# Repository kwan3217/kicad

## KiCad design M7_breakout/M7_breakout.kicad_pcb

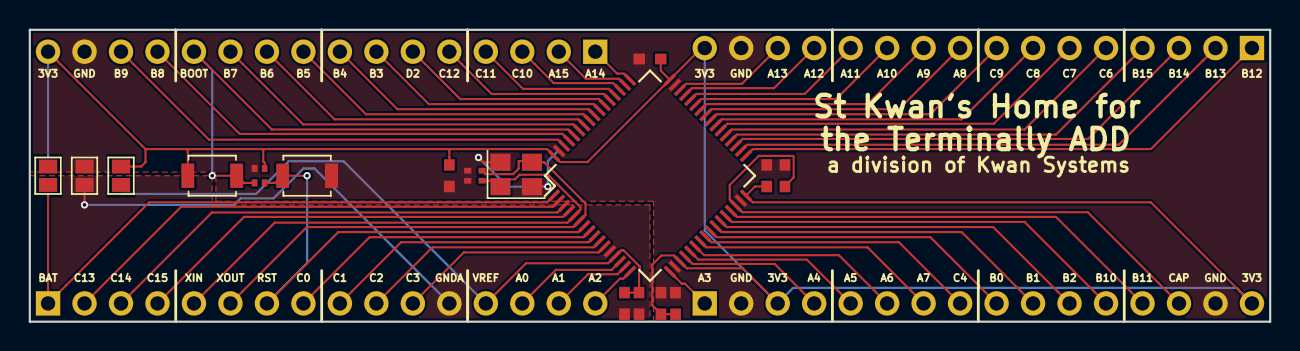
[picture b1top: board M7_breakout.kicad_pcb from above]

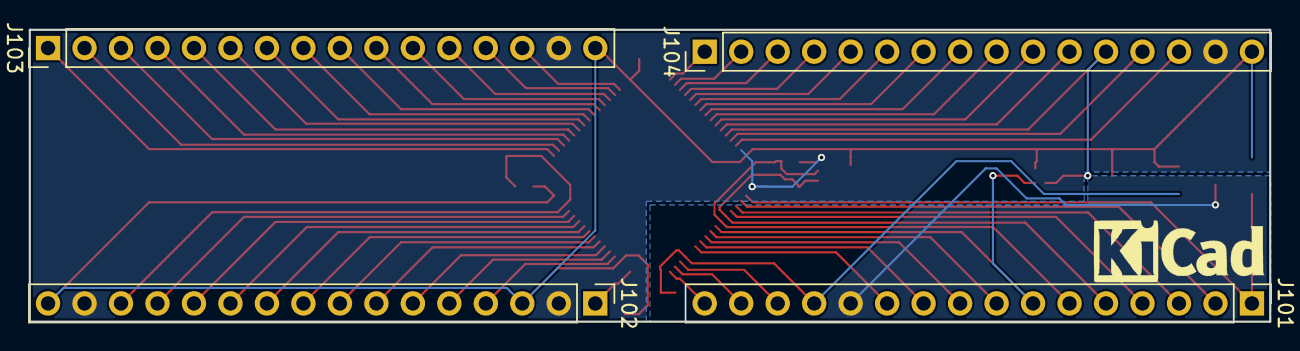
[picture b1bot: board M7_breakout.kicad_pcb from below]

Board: 2 copper layers, 86.4 x 20.3 mm, 21 parts (4 on the bottom side), 58 nets.

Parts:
C105: 22pF; R_Array_Convex_2x0402
C112: 1uF; SMD_0603
C113: 10nF; SMD_0603
C118, C130: 4.7uF; SMD_0603
C119, C132, C148, C164: 100nF; SMD_0603
J101, J102, J103, J104: Conn_01x16; Pin_Header_Straight_1x16_Pitch2.54mm
R107: 10k; R_Array_Convex_2x0402
S101, S112, S113: GS2
S107, S160: SW_SPST; SW_SPST_B3U-1000P
U101: STM32F722; LQFP-64_10x10mm_Pitch0.5mm
Y101: 12MHz; Crystal_SMD_3225-4pin_3.2x2.5mm

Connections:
+3V3: C118.2, C119.2, C132.2, C148.2, C164.2, J102.3, J102.16, J103.16, J104.16, R107.1, S101.2, S113.2, S160.1, U101.19, U101.32, U101.48, U101.64
/BOOT: J104.12, R107.3, S160.2, U101.60
/P2: J101.2, U101.2
/P3: J101.3, U101.3
/P4: J101.4, U101.4
/P8: J101.8, U101.8
/P9: J101.9, U101.9
/P10: J101.10, U101.10
/P11: J101.11, U101.11
/P14: J101.14, U101.14
/P15: J101.15, U101.15
/P16: J101.16, U101.16
/P17: J102.1, U101.17
/P20: J102.4, U101.20
/P21: J102.5, U101.21
/P22: J102.6, U101.22
/P23: J102.7, U101.23
/P24: J102.8, U101.24
/P25: J102.9, U101.25
/P26: J102.10, U101.26
/P27: J102.11, U101.27
/P28: J102.12, U101.28
/P29: J102.13, U101.29
/P33: J103.1, U101.33
/P34: J103.2, U101.34
/P35: J103.3, U101.35
/P36: J103.4, U101.36
/P37: J103.5, U101.37
/P38: J103.6, U101.38
/P39: J103.7, U101.39
/P40: J103.8, U101.40
/P41: J103.9, U101.41
/P42: J103.10, U101.42
/P43: J103.11, U101.43
/P44: J103.12, U101.44
/P45: J103.13, U101.45
/P46: J103.14, U101.46
/P49: J104.1, U101.49
/P50: J104.2, U101.50
/P51: J104.3, U101.51
/P52: J104.4, U101.52
/P53: J104.5, U101.53
/P54: J104.6, U101.54
/P55: J104.7, U101.55
/P56: J104.8, U101.56
/P57: J104.9, U101.57
/P58: J104.10, U101.58
/P59: J104.11, U101.59
/P61: J104.13, U101.61
/P62: J104.14, U101.62
/RESET: J101.7, R107.4, S107.1, U101.7
/VBAT: J101.1, S101.1, U101.1
/VCAP: C130.2, J102.14, U101.30
/VREF+: C112.2, C113.2, J101.13, S113.1, U101.13
/VSSA: C112.1, C113.1, J101.12, S112.1, U101.12
/XIN: C105.3, J101.5, U101.5, Y101.1
/XOUT: C105.4, J101.6, U101.6, Y101.3
GND: C105.1, C105.2, C118.1, C119.1, C130.1, C132.1, C148.1, C164.1, J102.2, J102.15, J103.15, J104.15, R107.2, S107.2, S112.2, U101.18, U101.31, U101.47, U101.63, Y101.2, Y101.4

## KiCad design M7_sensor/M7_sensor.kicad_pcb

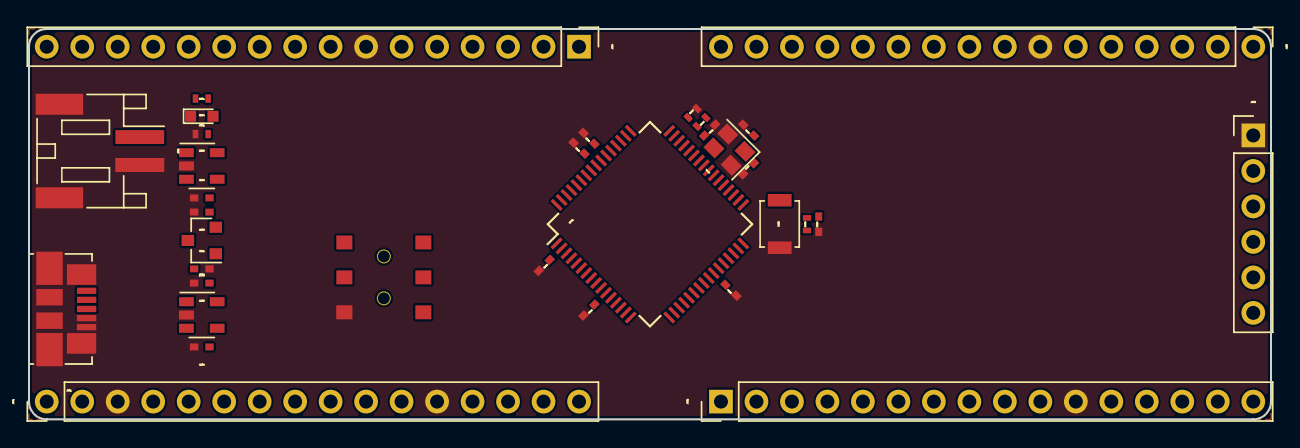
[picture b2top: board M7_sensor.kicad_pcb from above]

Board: 2 copper layers, 88.9 x 27.9 mm, 35 parts (1 on the bottom side), 23 nets, no tracks yet.

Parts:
C201, C205, C303, C304: 4.7uF; C_0402_NoSilk
C204, C402, C411, C426, C438, C442, C454: 100nF; C_0402_NoSilk
C440, C441: 22pF; C_0402_NoSilk
C456: 3.3uF; C_0402_NoSilk
D301: Yellow; LED_0603
D302: PMEG2005CT; SOT-23
J001: USB_OTG; USB_Micro-B_Molex_47346-0001
J301: Battery_Cell; JST_PH_S2B-PH-SM4-TB_02x2.00mm_Angled
J401, J402, J403, J404: CONN_01X16; Pin_Header_Straight_1x16_Pitch2.54mm
J405: CONN_01X06; Pin_Header_Straight_1x06_Pitch2.54mm
J701: Micro_SD_Card_SPI; MICROSD-SOCKET-PP
R304, R305, R438, R446: 10k; R_0402_NoSilk
R447: 22k; R_0402_NoSilk
S203: SW_DPDT_x2; SWITCH_DPDT_AZY0202
S438: SW_Push; SW_SPST_B3U-1000P
U201: MIC5319-3.3; SOT-23-5
U301: MCP73831; SOT-23-5
U401: ATSAMS70J; LQFP-64_10x10mm_Pitch0.5mm
Y440: 25MHz; Crystal_SMD_2520-4pin_2.5x2.0mm

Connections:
+3V3: C205.1, C402.1, C411.1, C426.1, C442.1, C454.1, J401.2, J401.11, J402.10, J403.10, J404.6, J405.3, J701.4, R438.1, U201.5
/BYPASS: C204.1, U201.4
/CS_SD: J402.4, J701.2
/D+: J001.3, J403.12
/D-: J001.2, J403.11
/ENABLE: S203.2, U201.3
/MISO0: J402.5, J701.7
/MOSI0: J402.6, J701.3
/OSC0: C440.2, J403.8, Y440.1
/OSC1: C441.2, J403.9, Y440.3
/PROG: R305.1, U301.5
/RESET: C438.2, J403.6, R438.2, S438.2
/RX0: J402.1, J405.4
/SCK0: J402.3, J701.5
/STAT+: D301.2, R304.1
/STAT-: D301.1, U301.1
/TX0: J402.2, J405.5
/VBUS+: C304.2, D302.1, J001.1, R304.2, R446.1, U301.4
/VBUS-: J403.14, R446.2, R447.1
/VDDC: C456.1, J402.9, J404.8
/VIN: C201.1, D302.3, S203.3, U201.1
/VLIPO: C303.1, D302.2, J301.1, U301.3
GND: C201.2, C204.2, C205.2, C303.2, C304.1, C402.2, C411.2, C426.2, C438.1, C440.1, C441.1, C442.2, C454.2, C456.2, J001.4, J001.5, J001.6, J301.2, J401.3, J401.12, J402.11, J403.7, J404.7, J405.1, J701.6, J701.9, R305.2, R447.2, S203.1, S438.1, U201.2, U301.2, Y440.2, Y440.4

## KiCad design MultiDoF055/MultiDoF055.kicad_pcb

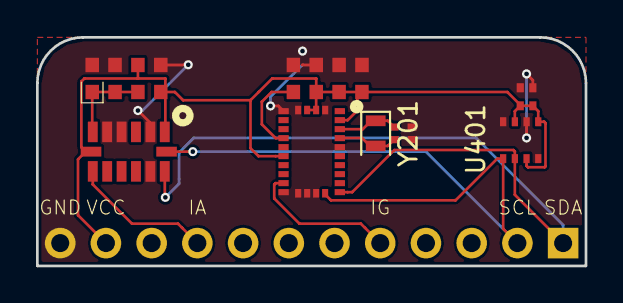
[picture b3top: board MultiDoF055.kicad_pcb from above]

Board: 2 copper layers, 30.5 x 12.7 mm, 15 parts (0 on the bottom side), 10 nets.

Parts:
C203, C209, C501, C505: 100nF; SMD_0603
C225: 120nF; SMD_0603
C226: 22pF; R_Array_Convex_2x0402
C228: 6.8nF; SMD_0603
C406: 100nF; R_Array_Convex_2x0402
C506: 10uF; SMD_0603_pol
J102: Conn_01x12; Pin_Header_Straight_1x12_Pitch2.54mm
R506: 100; SMD_0603
U201: BNO055
U401: BME280
U501: ADXL375
Y201: 32kiHz; Crystal_SMD_2012-2pin_2.0x1.2mm

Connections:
+3V3: C203.2, C225.1, C228.1, C406.1, C406.2, C501.1, J102.11, R506.1, U201.3, U201.4, U201.11, U201.28, U401.2, U401.6, U401.8, U501.1, U501.7
/ADXL_INT: J102.9, U501.8
/BNO055/CAP: C209.1, U201.9
/BNO055/XIN32: C226.1, U201.27, Y201.1
/BNO055/XOUT32: C226.2, U201.26, Y201.2
/BNO_INT: J102.5, U201.14
/HighAcc/VS: C505.1, C506.1, R506.2, U501.6
/SCL: J102.2, U201.19, U401.4, U501.14
/SDA: J102.1, U201.20, U401.3, U501.13
GND: C203.1, C209.2, C225.2, C226.3, C226.4, C228.2, C406.3, C406.4, C501.2, C505.2, C506.2, J102.12, U201.2, U201.5, U201.6, U201.15, U201.16, U201.17, U201.18, U201.25, U401.1, U401.5, U401.7, U501.2, U501.4, U501.5, U501.12

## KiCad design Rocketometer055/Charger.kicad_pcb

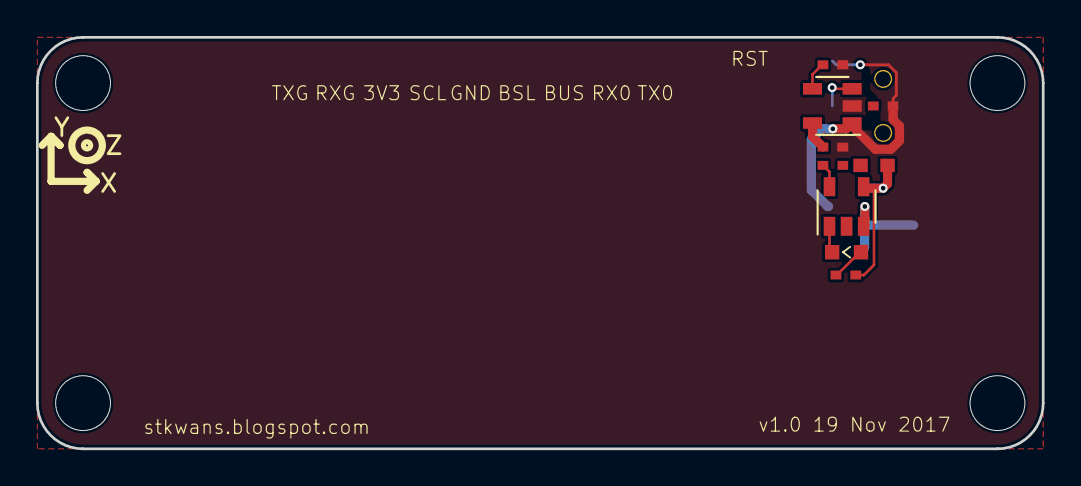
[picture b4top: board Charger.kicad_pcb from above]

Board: 2 copper layers, 55.9 x 22.9 mm, 18 parts (0 on the bottom side), 11 nets.

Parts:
C704: 1uF; SMD_0402
C714: 100nF; SMD_0402
C715: 4.7nF; SMD_0402
C802, C803: 4.7uF; SMD_0603
D801: YELLOW; D_0603
D802: DCC; SOT-23
J801: JST 2mm; SPARKFUN_JST_POWER
JP1, JP2, JP4, JP5: STAND-OFFTIGHT; STAND-OFF-TIGHT
R801: 10k; SMD_0402
R804: 1.5k; SMD_0402
S701: SPDT; SWITCH_DPDT_AZY0202
U501: MPU9250; Axis
U701: 3.3V; SOT-23-5
U801: MCP73831; SOT-23-5

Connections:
/GND: C802.2, C803.2, J801.-, R801.1, U801.2
/PROG: R801.2, U801.5
/Regulator/BYP: C714.1, U701.4
/Regulator/PWR_EN: S701.2, U701.3
/STAT+: D801.2, R804.2
/STAT-: D801.1, U801.1
/VBUS: C802.1, D802.1, R804.1, U801.4
/VLIPO: C803.1, D802.2, J801.+, U801.3
/VRAW: C704.1, D802.3, S701.1, U701.1
GND: C704.2, C714.2, C715.2, S701.3, U701.2
VCC: C715.1, U701.5

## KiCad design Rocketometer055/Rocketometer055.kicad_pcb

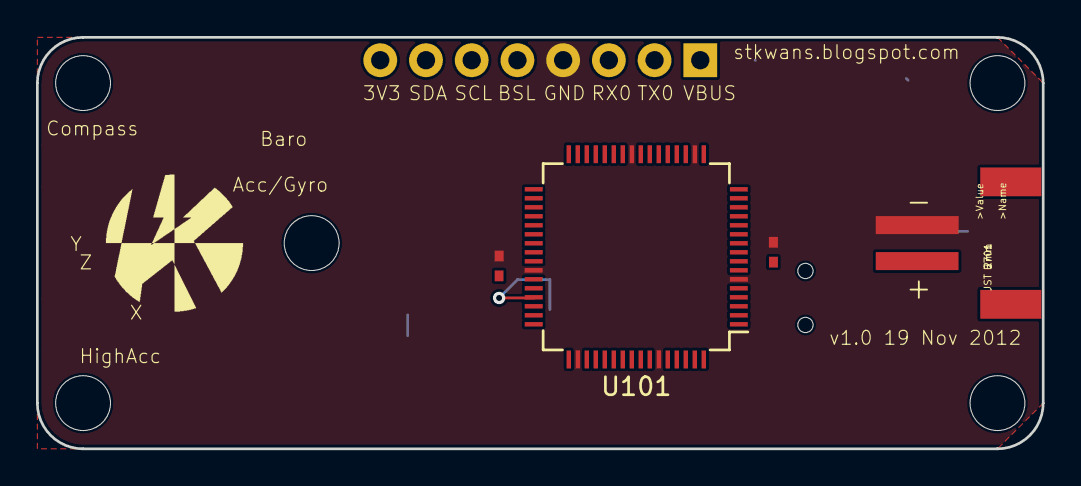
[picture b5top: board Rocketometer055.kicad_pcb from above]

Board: 2 copper layers, 55.9 x 22.9 mm, 22 parts (0 on the bottom side), 9 nets.

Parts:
B701: JST 2mm; JST-2-SMD
C405: 18pF; SMD_0402
C443: 100nF; SMD_0402
D050: BLUE; LED-0603
D301: YELLOW; LED-0603
D401: HSMF-C118
J001: USB_MICROB; UB-MC5BR3-SD204-4S
J102: Micro_SD_Card_Det_Hirose_DM3AT; MICROSD-SOCKET-PP
J401: M07; 1X08
JP1, JP2, JP3, JP4, JP5: STAND-OFFTIGHT; STAND-OFF-TIGHT
S157: SPST; B3U-1000P
S201: SPDT; AYZ0202
S456: SOLDERJUMPERNO; SJ_2S-NO
U101: LPC2148; LQFP-64_10x10mm_Pitch0.5mm
U$1, U$5: KWAN_ACC
U$4: AXES
U$6: OSHW_ACC

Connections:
/CS0: J102.2, U101.45
/MISO0: J102.7, U101.29
/MOSI0: J102.3, U101.30
/RST: S157.2, U101.57
/RX0: J401.3, U101.21
/SCK0: J102.5, U101.27
/VBUS: J001.1, J401.1
GND: B701.-, C405.1, C443.2, J001.5, J001.6, J102.6, J102.9, J102.10, J102.11, J401.4, S201.3, S456.1, U101.6, U101.18, U101.25, U101.42, U101.50, U101.59
VCC: C443.1, D401.1, J102.4, J401.8, U101.7, U101.23, U101.43, U101.49, U101.51, U101.63

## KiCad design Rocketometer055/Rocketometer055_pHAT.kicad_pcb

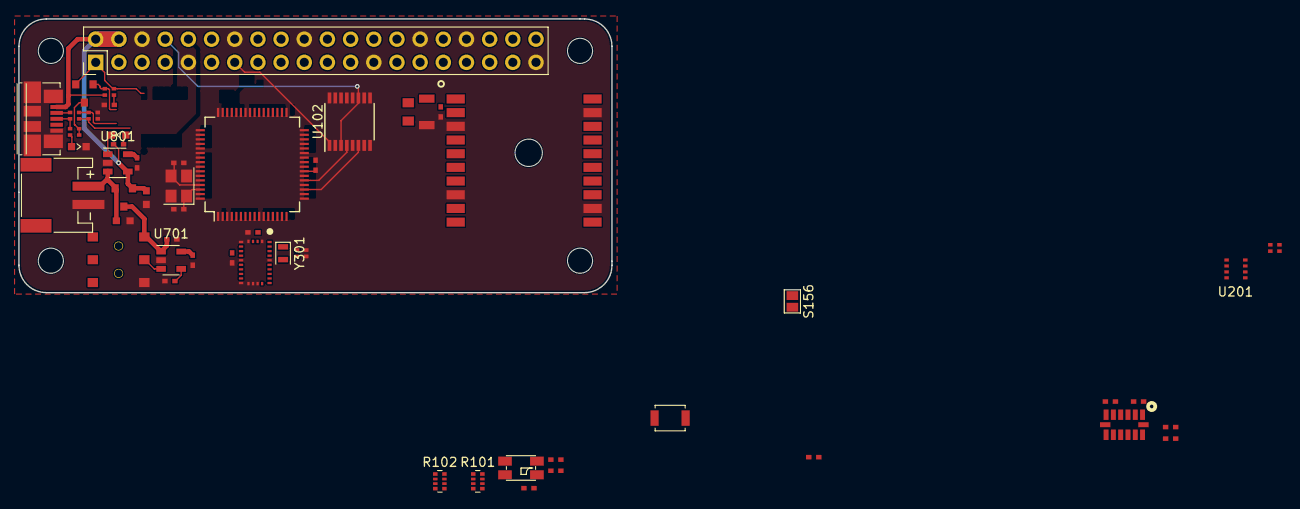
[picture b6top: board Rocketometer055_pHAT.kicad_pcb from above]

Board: 2 copper layers, 65.0 x 30.0 mm, 58 parts (0 on the bottom side), 49 nets.

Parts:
1PIN, 1PIN#2, 1PIN#3, 1PIN#4: P***; 1pin
B801: JST 2mm; SPARKFUN_JST_POWER
C116, C143, C151, C163, C401, C405, C501, C714: 100nF; SMD_0402
C123, C406, C704: 1uF; SMD_0402
C161, C162: 33pF; SMD_0402
C206: 100nF; R_Array_Convex_2x0402
C303, C309: 0.1uF; SMD_0402
C326, C623: 22pF; R_Array_Convex_2x0402
C503: 10uF; SMD_1206
C715: 4.7nF; SMD_0402
C802, C803: 4.7uF; SMD_0603
D101: HSMF-C118
D650: BLUE; D_0603
D801: YELLOW; D_0603
D802: DCC; SOT-23
J101: RPi_GPIO; Pin_Header_Straight_2x20_Pitch2.54mm
J102: Micro_SD_Card_Det_Hirose_DM3AT; MICROSD-SOCKET-PP
J601: USB_MICROB; USB_Micro-B_Molex_47346-0001
L501: Ferrite; SMD_0805
Q650: PMOS; SOT-23
R101: 10k; R_Array_Convex_4x0402
R102: 1.5k; R_Array_Convex_4x0402
R406: 100; SMD_0402
R611: 22k; SMD_0402
R623: 33; R_Array_Convex_2x0402
R650: 1.5k; R_Array_Convex_2x0402
R651: 10k; R_Array_Convex_2x0402
R801: 10k; SMD_0402
R804: 1.5k; SMD_0402
S156: SOLDERJUMPERNO; GS2
S157: SPST; SW_SPST_B3U-1000P
S701: SPDT; SWITCH_DPDT_AZY0202
U101: LPC2148; LQFP-64_10x10mm_Pitch0.5mm
U102: 74CBTLV3257; SSOP-16_3.9x4.9mm_Pitch0.635mm
U201: BME280
U301: BNO085; BNO055
U401: ADXL375
U501: FGPMMOPA6H
U701: 3.3V; SOT-23-5
U801: MCP73831; SOT-23-5
Y101: 12MHz; Crystal_SMD_Abracon_ABM8G-4pin_3.2x2.5mm
Y301: 32kiHz; Crystal_SMD_2012-2pin_2.0x1.2mm

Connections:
/ACCINT: U101.46, U301.14
/BNO055/CAP: C309.2, U301.9
/BNO055/XIN32: C326.1, U301.27, Y301.1
/BNO055/XOUT32: C326.2, U301.26, Y301.2
/CS0: J102.2, U101.45
/Charger/PROG: R801.2, U801.5
/Charger/STAT+: D801.2, R804.2
/Charger/STAT-: D801.1, U801.1
/DB: D101.4, R102.4
/DG: D101.3, R102.1
/DR: D101.2, R102.2
/FIX: J101.7, U101.35, U501.5
/GPS/VGPS: C501.2, C503.2, L501.2, U501.1
/GPS_RX: U102.9, U501.10
/GPS_TX: U101.34, U102.5, U501.9
/HighAcc/VS: C405.1, C406.1, R406.2, U401.6
/LPC_RX0: U101.21, U102.4
/LPC_TX0(PWMR): R102.7, U101.19, U102.6
/LPC_TX1: U101.33, U102.10
/MISO0: J102.7, U101.29
/MOSI0: J102.3, U101.30
/PI_RX: J101.10, U102.7
/PI_TX: J101.8, U102.3, U102.11
/PPS: J101.12, U101.2, U501.13
/PWMB: R102.5, U101.1
/PWMG: R102.8, U101.31
/RST: J101.11, R101.2, S157.2, U101.57
/Regulator/BYP: C714.1, U701.4
/Regulator/PWR_EN: S701.2, U701.3
/S: J101.13, R101.1, U102.1
/SCK0: J102.5, U101.27
/SCL: J101.5, R101.3, U101.37, U201.4, U301.19, U401.14
/SDA(BSL): J101.3, R101.4, U101.41, U201.3, U301.20, U401.13
/USB/CONN_D+: J601.3, R623.4, R650.1
/USB/CONN_D-: J601.2, R623.3
/USB/USB_LIGHT+: Q650.3, R650.3, R650.4
/USB/USB_LIGHT-: D650.2, R650.2
/USBD+: C623.2, R623.1, U101.10
/USBD-: C623.1, R623.2, U101.11
/USB_ON: R611.2, R651.1, U101.58
/USB_SOFTCONNECT: Q650.1, R651.3, U101.17
/VBUS: C802.1, D802.1, J101.2, J101.4, J601.1, R651.4, R804.1, U801.4
/VLIPO: B801.+, C803.1, D802.2, U501.4, U801.3
/VRAW: C704.1, D802.3, S701.1, U701.1
/XTAL1: C162.2, U101.62, Y101.1
/XTAL2: C161.2, U101.61, Y101.3
GND: B801.-, C116.2, C123.2, C143.2, C151.2, C161.1, C162.1, C163.2, C206.3, C206.4, C303.1, C309.1, C326.3, C326.4, C401.2, C405.2, C406.2, C501.1, C503.1, C623.3, C623.4, C704.2, C714.2, C715.2, C802.2, C803.2, D650.1, J101.6, J101.9, J101.14, J101.20, J101.25, J101.30, J101.34, J101.39, J102.6, J102.9, J102.10, J601.5, J601.6, R611.1, R801.1, S156.1, S701.3, U101.6, U101.18, U101.25, U101.42, U101.50, U101.59, U102.8, U102.15, U201.1, U201.5, U201.7, U301.2, U301.5, U301.6, U301.10, U301.15, U301.16, U301.17, U301.18, U301.25, U401.2, U401.4, U401.5, U401.12, U501.3, U501.8, U501.12, U501.19, U701.2, U801.2, Y101.2, Y101.4
unnamed: S156.2, S157.1
VCC: C116.1, C123.1, C143.1, C151.1, C163.1, C206.1, C206.2, C303.2, C401.1, C715.1, D101.1, J101.1, J101.17, J102.4, L501.1, Q650.2, R101.5, R101.6, R101.7, R101.8, R406.1, R651.2, U101.7, U101.23, U101.43, U101.49, U101.51, U101.63, U102.16, U201.2, U201.6, U201.8, U301.3, U301.4, U301.11, U301.28, U401.1, U401.7, U701.5

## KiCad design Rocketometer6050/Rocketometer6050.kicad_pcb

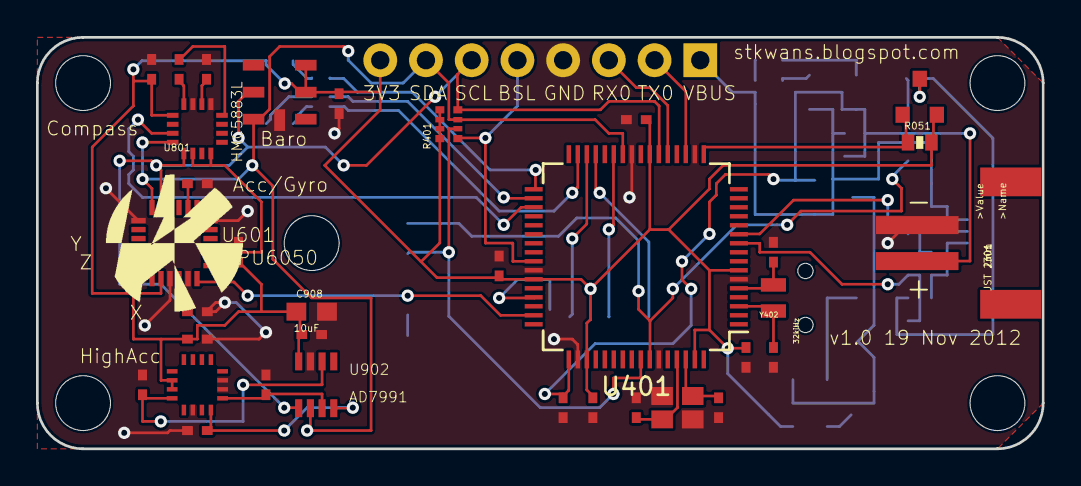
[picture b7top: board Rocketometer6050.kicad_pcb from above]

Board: 2 copper layers, 55.9 x 22.9 mm, 73 parts (0 on the bottom side), 49 nets.

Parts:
C010, C204, C423: 1uF; SMD_0402
C020, C030: 22pF; SMD_0402
C101, C214, C443, C449, C451, C463, C610, C613, C802, C904, C905, C907, C916: 100nF; SMD_0402
C215: 4.7nF; SMD_0402
C301, C302, C810, C914: 4.7uF; SMD_0402
C403, C405: 18pF; SMD_0402
C461, C462: 33pF; SMD_0402
C620: 2.2nF; SMD_0402
C808: 220nF; SMD_0402
C908: 10uF; 0603-CAP
D050: BLUE; LED-0603
D301: YELLOW; LED-0603
D302: DCC; SOT-23
D401: HSMF-C118
J001: USB_MICROB; UB-MC5BR3-SD204-4S
J301: JST 2mm; JST-2-SMD
J401: M07; 1X08
J701: Micro_SD_Card_Det_Hirose_DM3AT; MICROSD-SOCKET-PP
JP1, JP2, JP3, JP4, JP5: STAND-OFFTIGHT; STAND-OFF-TIGHT
Q050: PMOS; SOT-23
R010, R051, R301: 10k; 0402-RES
R011: 100k; 0402-RES
R020, R030: 33; 0402-RES
R031, R050, R302: 1.5k; 0402-RES
R401: 10k; CRA04
R402: 1.5k; CRA04
S201: SPDT; AYZ0202
S456: SOLDERJUMPERNO; SJ_2S-NO
S457: SPST; B3U-1000P
S458: B3U-1000P
U101: BMP180
U201: 3.3V; SOT-23-5
U301: MCP73831; SOT-23-5
U401: LPC2148; LQFP-64_10x10mm_Pitch0.5mm
U601: MPU6050; MPU60X0
U801: HMC5883L; 16LPCC
U901: ADXL377
U902: AD7991; SOT-23-8
U$1, U$5: KWAN_ACC
U$4: AXES
U$6: OSHW_ACC
Y401: 12MHz; CRYSTAL_SMD_2MM_2_5MM
Y402: 32kiHz; ABS06

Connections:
/ACCINT: U401.47, U601.12
/BSL: J401.5, R401.1, U401.41
/BYP: C214.1, U201.4
/COMPINT: U401.35, U801.15
/CONN_D+: J001.3, R030.1, R031.1
/CONN_D-: J001.2, R020.1
/CS0: J701.2, U401.45
/DB: D401.4, R402.2
/DG: D401.3, R402.1
/DR: D401.2, R402.4
/HMC5883L/C1: C810.2, U801.10
/HMC5883L/SETC: C808.2, U801.12
/HMC5883L/SETP: C808.1, U801.8
/HighAcc/XACC: C905.2, U901.5, U902.3
/HighAcc/YACC: C904.2, U901.4, U902.4
/HighAcc/ZACC: C916.2, U901.16, U902.6
/MISO0: J701.7, U401.29
/MOSI0: J701.3, U401.30
/MPU6050/N$1: C620.1, U601.20
/MPU6050/N$13: C610.2, U601.10
/N$2: R301.2, U301.5
/N$4: D301.1, U301.1
/N$5: D301.2, R302.2
/N$6: D050.2, Q050.3, R031.2
/N$7: D050.1, R050.2
/PWMB: R402.7, U401.34
/PWMG: R402.8, U401.31
/PWMR: R402.5, U401.33
/PWR_EN: S201.2, U201.3
/RST: R401.2, S457.2, U401.57
/RTXC1: C403.2, U401.3, Y402.1
/RTXC2: C405.2, U401.5, Y402.2
/RX0: J401.3, U401.21
/SCK0: J701.5, U401.27
/SCL0: J401.6, R401.4, U101.5, U401.22, U601.23, U801.1, U902.1
/SDA0: J401.7, R401.3, U101.6, U401.26, U601.24, U801.16, U902.2
/TX0: J401.2, U401.19
/USBD+: C030.1, R030.2, U401.10
/USBD-: C020.1, R020.2, U401.11
/USB_LIGHT: Q050.1, R051.1, U401.17
/USB_ON: R010.2, S458.1, U401.58
/VBUS: C010.1, C302.1, D302.1, J001.1, J401.1, R010.1, R011.2, R302.1, U301.4
/VIN+: C204.1, D302.3, S201.1, U201.1
/VLIPO: C301.1, C449.2, D302.2, J301.2, U301.3, U401.49
/XTAL1: C462.2, U401.62, Y401.1
/XTAL2: C461.2, U401.61, Y401.3
GND: C010.2, C020.2, C030.2, C101.1, C204.2, C214.2, C215.2, C301.2, C302.2, C403.1, C405.1, C423.2, C443.2, C449.1, C451.2, C461.1, C462.1, C463.2, C610.1, C613.2, C620.2, C802.1, C810.1, C904.1, C905.1, C907.2, C908.2, C914.2, C916.1, J001.5, J001.6, J301.1, J401.4, J701.6, J701.9, J701.11, J701.12, R011.1, R050.1, R301.1, S201.3, S456.1, S458.2, U101.7, U201.2, U301.2, U401.6, U401.18, U401.25, U401.42, U401.50, U401.59, U601.1, U601.9, U601.11, U601.18, U801.9, U801.11, U901.2, U901.6, U901.7, U902.7, Y401.2, Y401.4
unnamed: S456.2, S457.1
VCC: C101.2, C215.1, C423.1, C443.1, C451.1, C463.1, C613.1, C802.2, C907.1, C908.1, C914.1, D401.1, J401.8, J701.4, Q050.2, R051.2, R401.5, R401.6, R401.7, R401.8, U101.2, U101.3, U201.5, U401.7, U401.23, U401.43, U401.51, U401.63, U601.8, U601.13, U801.2, U801.4, U801.13, U901.14, U901.15, U902.8

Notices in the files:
MultiDoF055/MultiDoF055.kicad_pcb:
Released under the Creative Commons Attribution Share-Alike 3.0 License
http://creativecommons.org/licenses/by-sa/3.0
